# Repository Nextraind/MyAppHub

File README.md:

# ATtiny85Mario

Read about the software and hardware of ATtiny85Mario here:
https://shepherdingelectrons.blogspot.com/2020/01/tinymario.html

and the construction of a handset to play ATtiny85Mario in:

https://shepherdingelectrons.blogspot.com/2020/03/attiny-mario-handset.html

Mario-style game with sound effects and music on twin OLED displays driven by ATtiny85 AVR. Having fun with the multiple challenges of working with small system constraints! :-)

**TinyMario**
Source code for Mario.  For music and sound effects to work, the EEPROM must be correctly burned first (see BurnEEPROM_ATtiny85 sketch)

- OLED code is derived from bitbang2's super fast code:
https://github.com/bitbank2/oled_turbo
- Mario theme music is taken from Mike Marburg's transcription of the score:
https://github.com/mikemalburg/arduino_annoyotrons_piezo/tree/master/annoy_piezo_mario_overworld
- Mario animation pixel art:
https://www.hackster.io/138689/pixel-art-on-oled-display-7f8697

**BurnEEPROM_ATtiny85**

Arduino sketch to compress the music and sound effects, then burn to ATTiny85 EEPROM

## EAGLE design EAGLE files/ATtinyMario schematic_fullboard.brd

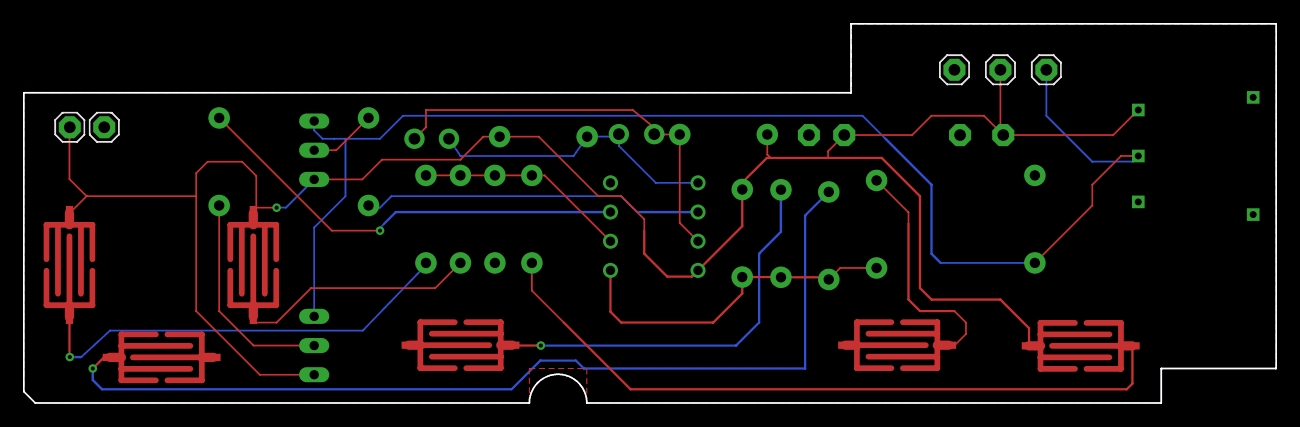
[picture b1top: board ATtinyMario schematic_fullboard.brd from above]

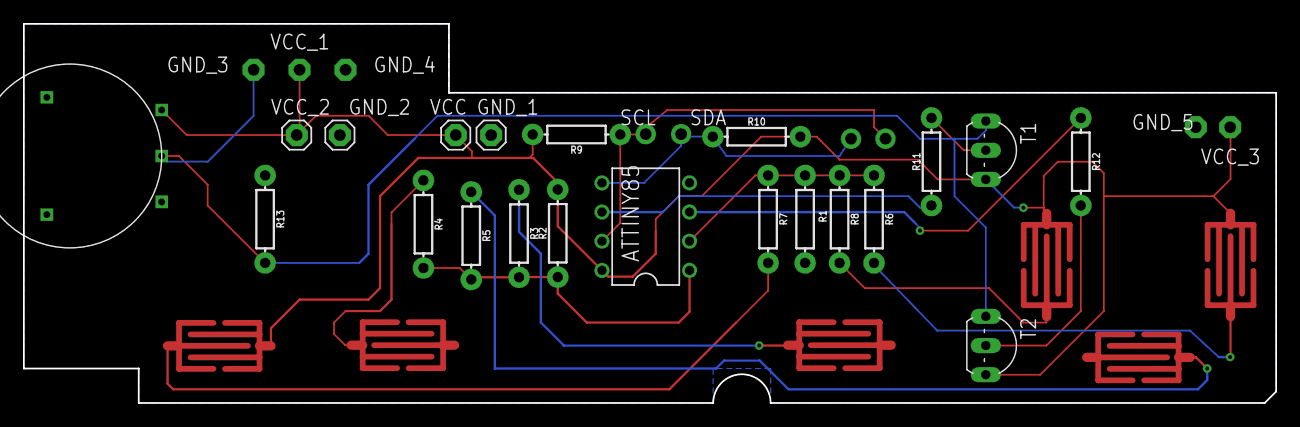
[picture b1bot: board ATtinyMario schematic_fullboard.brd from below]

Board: 2 copper layers, 109.0 x 33.0 mm, 36 parts (23 on the bottom side), 17 nets.

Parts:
ATTINY85: ATTINY85; PDIP08_300MIL
GND_1, GND_2, GND_3, GND_4, GND_5: 1X01
R1, R2, R11, R12: 1k; AXIAL-0.3
R3, R6, R9, R10: 10k; AXIAL-0.3
R4, R7: 22k; AXIAL-0.3
R5, R8: 47k; AXIAL-0.3
R13: 4.7k; AXIAL-0.3
SCL, SCL1: 1X01-CLEANBIG
SDA, SDA1: 1X01-CLEANBIG
T1, T2: 2N2222; TO92-EBC-OVAL
U$1, U$2, U$3, U$4, U$6, U$7: PCB_BUTTON_DEVICE; PCB_BUTTON
U$5: VOLUME_WHEEL; VOLUME_PCB
VCC: 1X01
VCC_1, VCC_2, VCC_3: 1X01

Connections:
AUDIO: GND_3.1, R13.P$2, T1.E, T2.E, U$5.SIGNAL
BUTTON1_GND: R3.P$1, U$1.PAD1
BUTTON2_GND: R4.P$1, U$6.PAD1
BUTTON3_GND: R5.P$1, U$7.PAD1
BUTTON4_VCC: R6.P$2, U$2.PAD2
BUTTON5_VCC: R7.P$2, U$3.PAD2
BUTTON6_VCC: R8.P$2, U$4.PAD2
GND: ATTINY85.4, GND_1.1, GND_2.1, GND_4.1, GND_5.1, R1.P$2, R13.P$1, U$1.PAD2, U$5.GND, U$6.PAD2, U$7.PAD2
unnamed: ATTINY85.1, R2.P$1, R3.P$2, R4.P$2, R5.P$2
unnamed: ATTINY85.2, R1.P$1, R6.P$1, R7.P$1, R8.P$1
unnamed: R11.P$2, T1.B
unnamed: R12.P$2, T2.B
SCL: ATTINY85.7, R9.P$1, SCL.1, SCL1.1
SDA: ATTINY85.5, R10.P$1, SDA.1, SDA1.1
SPEAKER: ATTINY85.6, R11.P$1
SPEAKER2: ATTINY85.3, R12.P$1
VCC: ATTINY85.8, R2.P$2, R9.P$2, R10.P$2, T1.C, T2.C, U$2.PAD1, U$3.PAD1, U$4.PAD1, U$5.VCC, VCC.1, VCC_1.1, VCC_2.1, VCC_3.1

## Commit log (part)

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2021-05-19 security: SELinux: revert Samsung hard enforcing
2021-05-20 minor format changes
2021-05-20 Add license and README
2021-05-21 Saving
2021-05-29 Layout adjustments
2021-05-29 Geometry System working...
2021-05-30 align
2021-05-31 fix copyright notice
2021-06-03 Staging: android: lowmemorykiller.c
2021-06-03 :arrow_up: 1.2.4 :tada:
2021-06-04 USB: option: add Huawei E5331
2021-06-05 polish
2021-06-10 More data
2021-06-11 [maven-release-plugin] prepare release v0.5.0
2021-06-11 remove alias
2021-06-12 Fix rubocop issue
2021-06-14 WIP : DirectX rendering backend
2021-06-15 Primer commit
2021-06-19 optimizations
2021-06-19 fixes #80
2021-06-20 Translated Finnish
2021-06-20 Travis stuff
2021-06-22 Unreviewed, update chromium test expectations.
2021-06-23 Cleaned up docs
2021-06-23 New translations strings.xml (Macedonian)
2021-06-24 Initial data
2021-06-26 Script update.
2021-06-27 Minor code optimization
2021-06-28 Testing data generated
2021-06-29 ALSA: hda - hdmi: Fallback to ALSA allocation when selecting CA
2021-06-30 Initial github commit
2021-06-30 fix stuff
2021-07-01 popup fix
2021-07-04 Modified README
2021-07-07 Cleanup [skip hazardlib]
2021-07-07 Add __init__.py
2021-07-10 update modes file
2021-07-11 Shortened
2021-07-11 Small typo.
2021-07-14 Version bump to 0.8.2
2021-07-15 Fixed various issues
2021-07-18 Add vimrc
2021-07-20 upgraded to parent 2.4.0
2021-07-20 build: Updating mediawiki/mediawiki-codesniffer to 0.10.1
2021-07-21 [MERGE] trunk
2021-07-21 Added Analytics
2021-07-22 Revert "sched: Add missing call to calc_load_exit_idle()"
2021-07-22 sched: s/do_each_thread/for_each_process_thread/ in core.c
2021-07-25 Updating .gitignore.
2021-07-25 kernel/resource.c: fix stack overflow in __reserve_region_with_split()
2021-07-27 license.
2021-07-28 remove stale comment
2021-07-29 release 0.9.0
2021-07-30 Blub
2021-07-30 Added error handler
2021-07-31 [3rd-party feeds] Update.
2021-08-01 fixes for tests
2021-08-03 updating travis
2021-08-03 small code refactor
2021-08-05 Gradle 4.5.1
2021-08-06 remove dist folder
2021-08-07 0.1.25
2021-08-08 oom_kill: has_intersects_mems_allowed() needs rcu_read_lock()
2021-08-09 4.0.9
2021-08-10 comments removed
2021-08-10 use new api
2021-08-11 MAINT: comment
2021-08-12 Test...
2021-08-13 - fix
2021-08-13 new packages
2021-08-15 new v
2021-08-16 Add .htaccess
2021-08-16 dict
2021-08-18 util.sh
2021-08-19 ring-buffer: Prevent overflow of size in ring_buffer_resize()
2021-08-21 Correct typo in README
2021-08-22 removed unused lines
2021-08-26 little corrections
2021-08-26 Release v4.0.0
2021-08-27 Add .pre for next release
2021-08-27 dm snapshot: fix data corruption
2021-08-30 write
2021-08-30 angularjs
2021-09-01 chore(package): update coveralls to version 2.12.0
2021-09-02 Release v2.6.0
2021-09-02 Removed alert
2021-09-04 Clean and consolidate export code #190
2021-09-07 updates template files
2021-09-08 Cleanup and documentation
2021-09-09 add contact page
2021-09-09 update typo
2021-09-10 resume update
2021-09-10 iteration of enterprise row model
2021-09-11 KVM: x86: move steal time initialization to vcpu entry time
2021-09-12 add reset
2021-09-12 [Dev Deps] update `tape`
2021-09-13 fix permission
2021-09-14 few more tests
2021-09-14 Fix README [ci skip]
2021-09-15 updated parameters
2021-09-16 lots of fixes
2021-09-16 haha
2021-09-17 Update yara submodule
2021-09-17 Lead développeur python / django
2021-09-19 ALSA: hda - Fix typo in checking IEC958 emphasis bit
2021-09-21 ci release
2021-09-21 Added meta tags
2021-10-03 improve test coverage
2021-10-03 Fixed some warnings from Codacy
2021-10-03 add newline
2021-10-10 add share
2021-10-10 Fix merge errors
2021-10-10 Fixed a couple typos
2021-10-17 Dutch translation
2021-10-24 Added commenting
2021-10-24 panel
2021-10-24 Added Project
2021-10-24 Remove bad import
2021-11-07 [maven-release-plugin] prepare release v2.0.2
2021-11-07 release 1.4
2021-11-12 feat: initial commit
2021-11-12 Update figure
2021-11-14 - package version
2021-11-14 Cleaning up...
2021-11-14 Update toc
2021-11-20 vendor
2021-11-27 remove comment
2021-11-28 Modified README.md
2021-11-28 Update build number
2021-11-29 add generated files
2021-11-29 Add coveralls badge
2021-12-01 Whitespace cleanup.
2021-12-01 * Updated docs
2021-12-02 Add clean script
2021-12-05 credits
2021-12-10 prep release
2021-12-12 rake translation:sync
2021-12-12 editorconfig
2021-12-13 init fix
2021-12-19 motivation
2021-12-26 added static files
2021-12-26 chore: build
2022-01-02 main.css
2022-01-06 update lint rules
2022-01-06 Update output.
2022-01-09 add script
2022-01-09 Update Gold Magic 800 - Level 16
2022-01-09 adding code
2022-01-12 Added missing dep
2022-01-15 Correct wording
2022-01-16 Improved UI
2022-01-23 composer install
2022-01-23 BRAMA
2022-02-13 add books
2022-02-16 Improved Readme
2022-02-20 Version 0.5
2022-02-20 new token
2022-02-27 Add sponsor
2022-03-06 Visual changes
2022-03-06 udpating readme [ci skip]
2022-03-12 dependencies update
2022-03-12 Added doc comments
2022-03-13 swift version
2022-03-20 roll version
2022-03-20 Switch to GitHub Actions
2022-03-20 New translations 03_p01_ch07_03.md (Turkish)
2022-03-25 Maven artifacts for SWI Prolog KR Interface version \t\t\t\t\t\t1.1.6-SNAPSHOT
2022-03-25 Fix travis config
2022-03-26 Remove debugging code.
2022-03-27 Back button
2022-03-27 Updating DownloadACEWorld.bat with latest ACE-World-Database release
2022-03-27 working on custom banner
2022-03-27 Pushing changed Database
2022-04-02 Adding gitignore.
2022-04-10 Bump to v0.3.1
2022-04-13 Regenerate schemas
2022-04-13 [maven-release-plugin] prepare release 1.1.4
2022-04-13 hfs,hfsplus: cache pages correctly between bnode_create and bnode_free
2022-04-13 Updating Docs
2022-04-18 ignore build folder
2022-04-18 indentation update
2022-04-18 genhd: check for int overflow in disk_expand_part_tbl()
2022-04-22 mm: remove gup_flags FOLL_WRITE games from __get_user_pages()
2022-04-22 Add package-lock
2022-04-24 Improve tests
2022-04-27 does this work?
2022-04-29 use travis
2022-04-29 apriori
2022-05-09 f2fs: support data flush in background
2022-05-09 Regenerate gemspec for version 0.0.10
2022-05-15 Updated package dependencies.
2022-05-17 Added logout button
2022-05-17 0.1.6
2022-05-20 removed build files
2022-05-20 orientation
2022-05-21 Small change.
2022-05-21 removed extra whitespace
2022-05-21 removed tmp files
2022-05-21 truncate
2022-05-23 user page
2022-05-26 bnx2x: fix panic when TX ring is full
2022-05-26 net: l2tp_eth: fix kernel panic on rmmod l2tp_eth
2022-05-28 Added config files
2022-05-30 Set development version
2022-05-30 fix for the fix
2022-06-01 staging: binder: fix usage of uninit scalar in binder_transaction()
2022-06-04 Various code cleanups
2022-06-04 bump to 0.7.0
2022-06-04 License Added
2022-06-06 fixed schema
2022-06-06 Translated using Translate.Akeeba (Portuguese (Brazil))
2022-06-08 v0.3.12
2022-06-08 New commit, no message
2022-06-08 Updating companies.html via Laneworks CMS Publish
2022-06-08 Refactor everything
2022-06-12 Move to ../doc/emacs/, misc/
2022-06-13 Auto commit without commit message.
2022-06-13 cpufreq: cpu-boost: Use hotplug thread infrastructure
2022-06-15 Removing unused code.
2022-06-19 Fixed strings
2022-06-29 Add code.
2022-06-29 V8 deoptimization prevention updates
2022-06-29 Typo Fixes
2022-06-29 staging: comedi: comedi_compat32.c: fix COMEDI_CMD copy back
2022-07-11 decompressor: Add LZ4 decompressor module
2022-07-11 build(deps): bump path-parse from 1.0.6 to 1.0.7
2022-07-11 Welcome
2022-07-14 v0.4.9
2022-07-14 Fix docs links
2022-07-14 remove semicolon
2022-07-22 Add missing test file
2022-07-22 fix typo in last commit
2022-07-26 rearranged files
2022-08-02 Update commands
2022-08-02 Try this.
2022-08-02 jenkins auto cleanup of old snapshots
2022-08-03 Input: i8042 - add PNP modaliases
2022-08-06 aacraid: prevent invalid pointer dereference
2022-08-07 running version
2022-08-08 Update welcome page
2022-08-08 Interface improvements
2022-08-10 Bumps version.
2022-08-14 Changed layout
2022-08-17 update codeclimate config
2022-08-19 OSX fixes
2022-08-19 New translations.
2022-08-20 sort
2022-08-31 Fixed #3
2022-09-01 ménage
2022-09-01 Copy fixes
2022-09-06 new documentation
2022-09-06 File rename
2022-09-07 Performance optimizations
2022-09-07 fixing text
2022-09-07 stupid typo
2022-09-24 Merging new upstream
2022-09-24 ext4: make sure the journal sb is written in ext4_clear_journal_err()
2022-09-24 Theme updates
2022-09-29 7.4.0
2022-09-29 update rubocop
2022-09-29 updated maven dependencies to latest
2022-10-02 Another update
2022-10-08 Replace tab with spaces
2022-10-17 msm: perf: Protect buffer overflow due to malicious user
2022-10-17 Working tests
2022-10-20 Updated Friulian translation
2022-10-20 [Jenkins] auto-formatting by clang-format version 6.0.1-14 (tags/RELEASE_601/final)
2022-10-20 chore: fix lint errors
2022-10-21 Fix email
2022-10-21 Update configuration
2022-10-23 added basic files
2022-10-23 Linux 3.10.64
2022-10-23 sanity checks
2022-10-23 A minor update
2022-10-24 Name changes
2022-10-24 ws / cs
2022-10-24 added notes
2022-10-29 add more details
2022-10-29 Link to docs
2022-10-29 Update all submodules
2022-10-29 Simple
2022-11-12 New translations ja-JP.yml (Japanese, Kansai)
2022-11-16 worker
2022-11-16 extract
2022-11-16 Bump version up.
2022-11-16 fixed typo in docstring
2022-11-19 Fix param name
2022-11-19 Added problems
2022-11-19 x86, mm: Trim memory in memblock to be page aligned
2022-11-20 style nit
2022-11-27 Create Vagrantfile
2022-11-27 Doc improvements.
2022-11-27 l10n: Updated Hebrew (he) translation to 100%
2022-12-01 version bumpup
2022-12-01 Missing files.
2022-12-02 Add to ingest machines.
2022-12-02 Update release process
2022-12-04 Prepare 0.15.0 release
2022-12-05 3.0.0-beta.2
2022-12-05 SQL: Rename SQL merged in PR
2022-12-05 Restructure repo
2022-12-06 chore(version): patch
2022-12-06 chore(package): update semantic-release to version 15.0.0
2022-12-06 zram: correct offset usage in zram_bio_discard
2022-12-07 Plugin $pluginName usando autotools. sin compilar.
2022-12-07 success
2022-12-07 Update naming
2022-12-07 sudo: false
2022-12-08 Renaming
2022-12-08 corrected documentation
2022-12-10 fixes #4
2022-12-10 Update tasks
2022-12-10 Fix build process
2022-12-10 Get French manual in sync with English
2022-12-12 evolution Jspresso mobile
2022-12-15 Arreglos varios
2022-12-15 Add missing comma.
2022-12-15 install depends
2022-12-31 Edited README file
2023-01-02 updated app
2023-01-02 11111
2023-01-02 tuned
2023-01-04 Translated using Weblate (Belarusian)
2023-01-04 fixing spec
2023-01-04 updated composer file
2023-01-04 drivers/i2c/busses: use correct type for dma_map/unmap
2023-01-08 Added new images
2023-01-08 Version 3.2.1
2023-01-08 removed binaries
2023-01-11 chore(package): update eslint to version 4.15.0
2023-01-15 fix travis builds
2023-01-15 Small addition.
2023-01-15 Add build status to README.
2023-01-15 usb: gadget: at91-udc: fix irq and iomem resource retrieval
2023-01-16 First code commit
2023-02-03 Added TODO's
2023-02-03 Fix compilation warning
2023-02-03 Cosmetic refactoring
2023-02-07 Imported upstream version 0.9.4.
2023-02-07 release v0.4.0
2023-02-11 - ‘tidal/#test.tidal#’ - ‘tidal/.#test.tidal’ / ‘tidal/test.tidal’
2023-02-12 New ACC version.
2023-02-13 - Segfault
2023-02-13 fix sysvfs symlinks
2023-02-13 md/raid1: submit_bio_wait() returns 0 on success
2023-02-14 mach-msm: mpdecision: small cleanup
2023-02-14 Forgot one
2023-02-17 [ADD] .editorconfig [ci skip]
2023-02-17 Upgrade packages
2023-02-25 Added readme mirroring plugin documentation
2023-02-28 Testing Travis CI
2023-02-28 Gradle build.
2023-02-28 Update: list of references.
2023-03-01 Optimizing imports
2023-03-04 ext4: make sure group number is bumped after a inode allocation race
2023-03-08 Accepted upstream
2023-03-08 New Test
2023-03-15 caif: fix NULL pointer check
2023-03-17 Add a notebook.
2023-03-23 Bumped up the version for new release

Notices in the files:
parts and their libraries:
SparkFun-Resistors: Licensing: Creative Commons ShareAlike 4.0 International - https://creativecommons.org/licenses/by-sa/4.0
